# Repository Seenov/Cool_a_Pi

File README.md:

# Cool_a_Pi 
Please find the 3D files and the Kicad files to make your own.

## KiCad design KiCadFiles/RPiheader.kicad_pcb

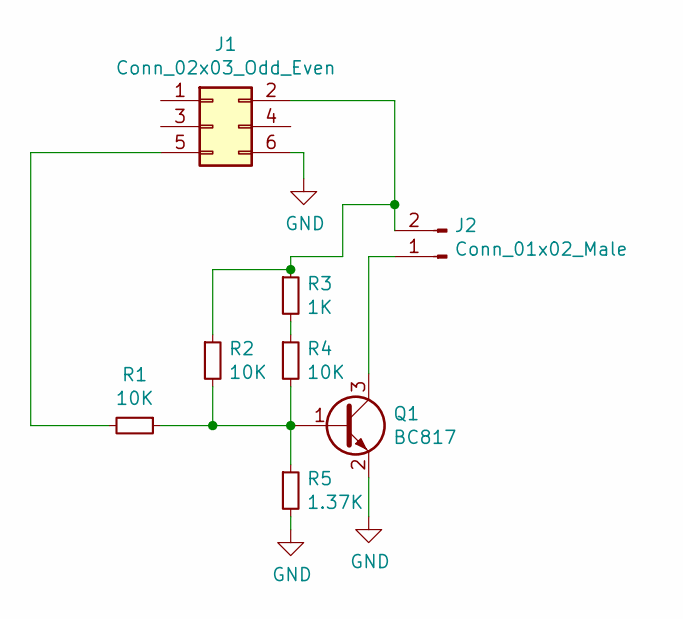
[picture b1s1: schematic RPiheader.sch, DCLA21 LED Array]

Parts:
J1: Conn_02x03_Odd_Even; PinHeader_2x03_P2.54mm_Vertical
J2: Conn_01x02_Male; R_0603_1608Metric
Q1: BC817; SOT-23
R1, R2, R4: 10K; R_0603_1608Metric
R3: 1K; R_0603_1608Metric
R5: 1.37K; R_0603_1608Metric

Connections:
GND: J1.6, Q1.2 (E), R5.2
unnamed: J1.2, J2.2, R2.1, R3.1
unnamed: J1.5, R1.2
unnamed: J2.1, Q1.3 (C)
unnamed: Q1.1 (B), R1.1, R2.2, R4.2, R5.1
unnamed: R3.2, R4.1

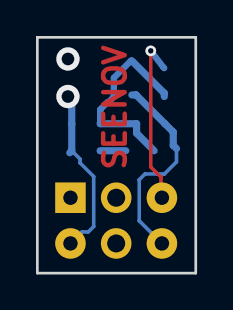
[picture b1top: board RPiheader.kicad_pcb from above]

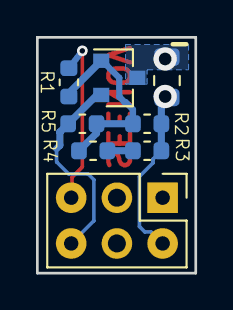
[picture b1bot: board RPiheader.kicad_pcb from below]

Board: 2 copper layers, 8.8 x 13.1 mm, 8 parts (8 on the bottom side), 6 nets.

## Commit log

2022-01-28 Update README.md
    Initial commit
2022-01-28 Add files via upload
    Initial commit.
2022-01-28 Initial commit.
    Initial commit. File paths may need to be updated.
2022-01-28 Picture with RPI 4B
